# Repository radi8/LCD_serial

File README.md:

# LCD_serial
3 wire serial drive for 16x2 LCD Display

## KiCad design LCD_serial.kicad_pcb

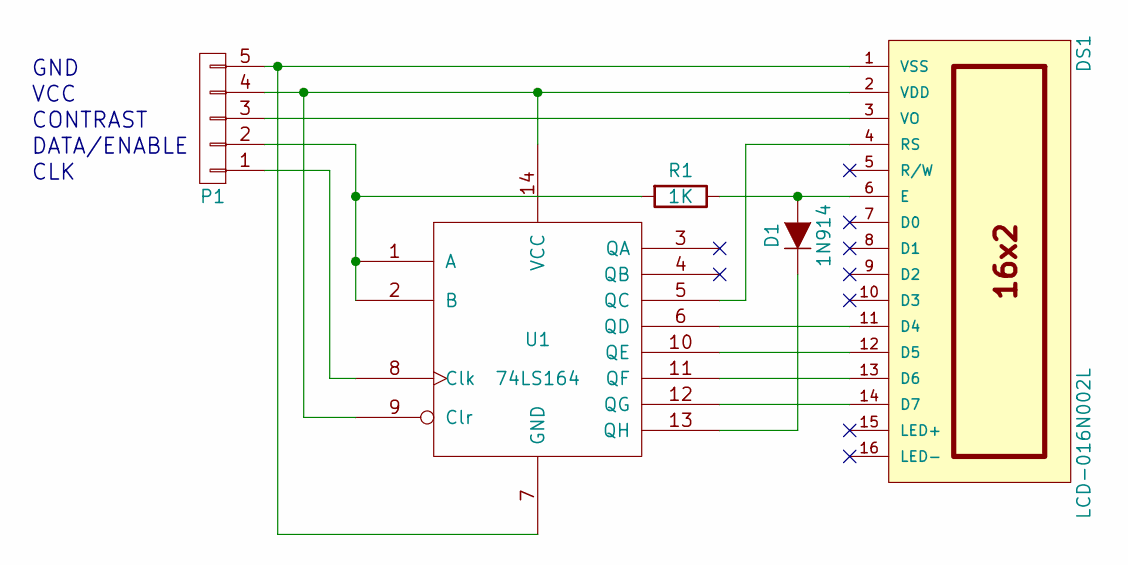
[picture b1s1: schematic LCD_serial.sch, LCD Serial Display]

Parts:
D1: 1N914; Diode_DO-35_SOD27_Horizontal_RM10
DS1: LCD-016N002L; Pin_Header_Straight_1x14
P1: CONN_01X05_GJ; Pin_Header_Straight_1x05
R1: 1K; R_1206_HandSoldering
U1: 74LS164; DIP-14_W7.62mm_LongPads

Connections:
unnamed: D1.1 (K), U1.13 (QH)
unnamed: D1.2 (A), DS1.6 (E), R1.1
unnamed: DS1.1 (VSS), P1.5, U1.7 (GND)
unnamed: DS1.2 (VDD), P1.4, U1.9 (Clr), U1.14 (VCC)
unnamed: DS1.3 (VO), P1.3
unnamed: DS1.4 (RS), U1.5 (QC)
unnamed: DS1.11 (D4), U1.6 (QD)
unnamed: DS1.12 (D5), U1.10 (QE)
unnamed: DS1.13 (D6), U1.11 (QF)
unnamed: DS1.14 (D7), U1.12 (QG)
unnamed: P1.1, U1.8 (Clk)
unnamed: P1.2, R1.2, U1.1 (A), U1.2 (B)

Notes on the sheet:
GND
VCC
CONTRAST
DATA/ENABLE
CLK

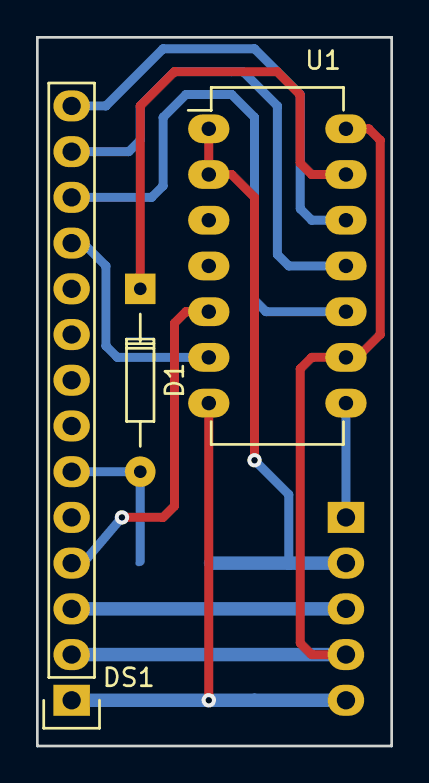
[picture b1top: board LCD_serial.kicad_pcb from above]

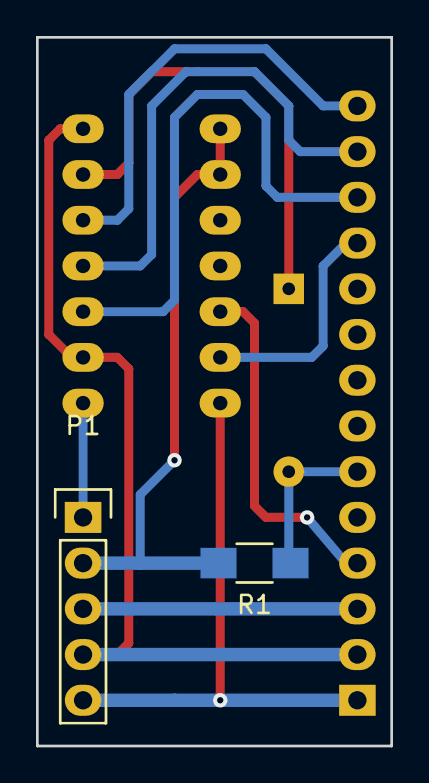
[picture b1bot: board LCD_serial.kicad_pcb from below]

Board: 2 copper layers, 19.7 x 39.4 mm, 5 parts (2 on the bottom side), 12 nets.

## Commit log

2016-01-27 Documentation & resource files added
2016-01-27 Added components Lib and adjusted power connections
2016-01-27 Starting on the PCB layout
2016-01-27 Rescue library created
2016-01-28 layout progress
2016-10-08 Fabricated version of board
